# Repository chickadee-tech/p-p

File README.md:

# Chickadee Tech Pololu Power Polystack Board #
This power board provides power to the base control board. It can either be used by mounting a Pololu voltage regulator directly to the pins or by using wire to connect to an existing regulator.

## Documentation ##
See the [wiki](https://github.com/chickadee-tech/p-p/wiki) for documentation.

## Polystack ##
This **power** board is part of the Polystack platform for modular microcontrol systems. More information on the platform can be found at [polystack.org](http://polystack.org).

## Support ##
If you need support with a board you own or have development questions please email support@chickadee.tech or check [chickadee.tech/support](https://chickadee.tech/support) for other ways to get support.

## Contributing ##
Please note that this project is released with a [Contributor Code of Conduct](CODE_OF_CONDUCT.md). By participating in this project you agree to abide by its terms.

### Setup ###
Components and footprints for PCB parts are not included in this repository. Instead, checkout the [chickadee-tech/kicad-libs](https://github.com/chickadee-tech/kicad-libs) repository in the same directory that this repository is checked out in. All part definitions should be relative so that they will load correctly.

### Pull requests ###
For fixes please submit a pull request to the original repository. After the pull request is merged, check the [Chickadee Tech Active Contributor Discount (ACD)](https://chickadee.tech/active-contributor) to see if you are eligible for a discount code to use on your next purchase.

### Derivatives ###
If developing your own version of the Pololu Power board please remove all Chickadee Tech trademarks and follow the [CC-BY license](LICENSE). While not required, please consider open sourcing your modifications so others can learn from your improvements. If you do email support@chickadee.tech and we may choose to add your project to the ACD.

You may also license the Polystack logo for free by emailing support@chickadee.tech. We'll ask for your gerbers to ensure the design complies with specifications laid out [here](https://github.com/chickadee-tech/polystack/wiki) and provide written permission to use the trademark after compliance has been demonstrated.

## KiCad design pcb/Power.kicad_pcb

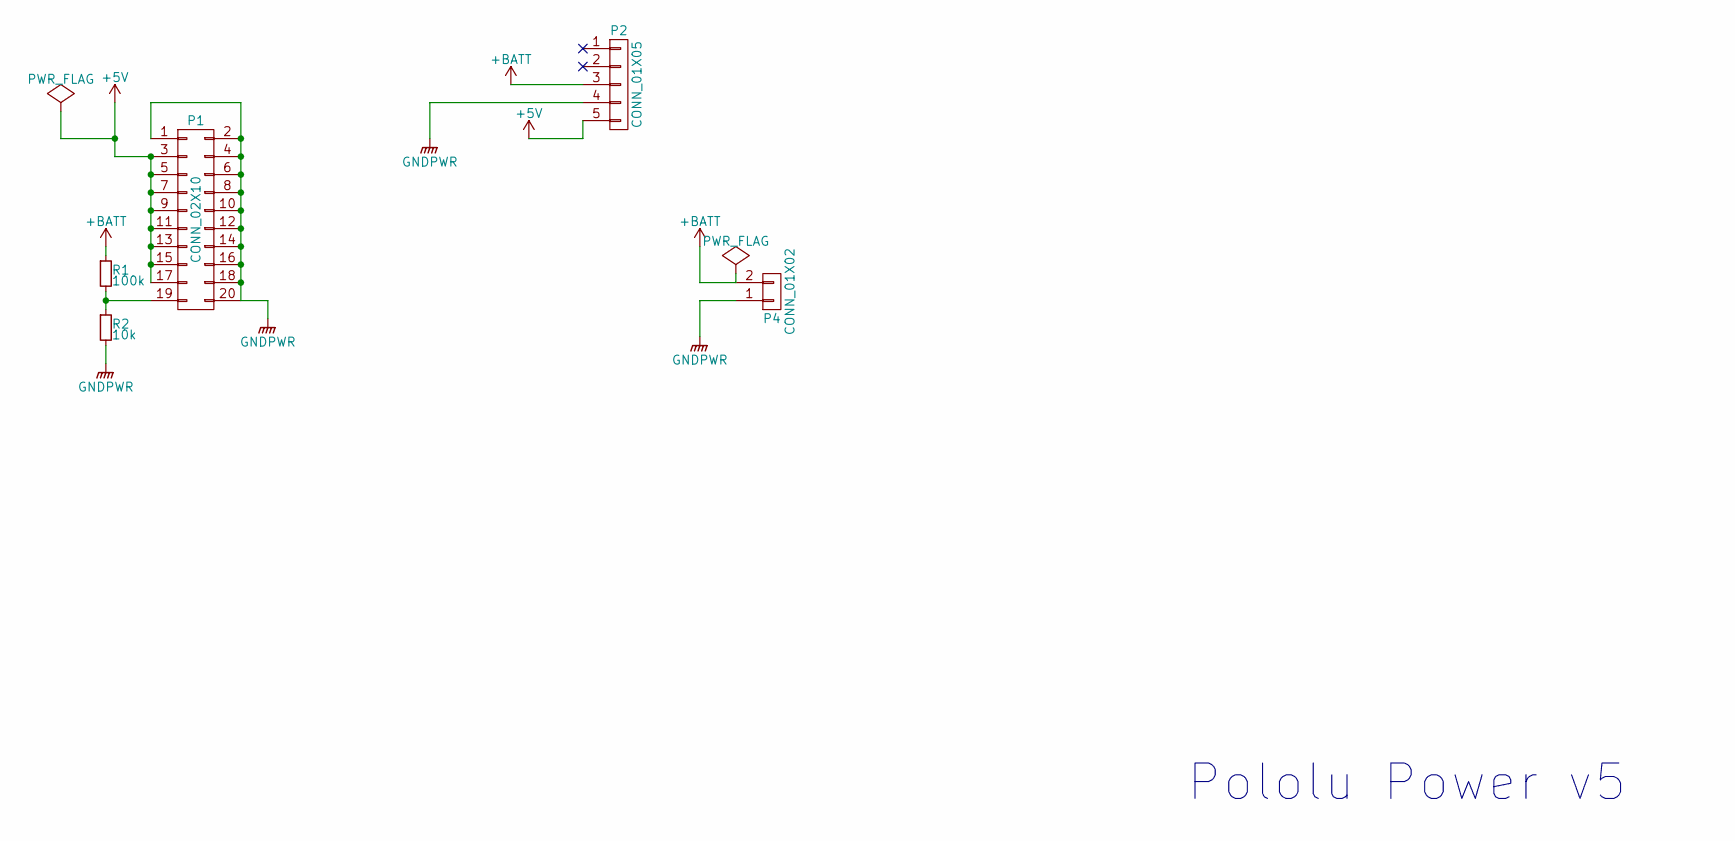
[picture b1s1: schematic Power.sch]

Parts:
P1: CONN_02X10; DF40-1.5mm-20pin-Receptacle
P2: CONN_01X05; Pin_Header_Straight_1x05
P4: CONN_01X02; 16awg_Pin_Header_Straight_1x02
R1: 100k; R_0603_HandSoldering
R2: 10k; R_0603_HandSoldering

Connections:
+5V: P1.3, P1.5, P1.7, P1.9, P1.11, P1.13, P1.15, P1.17, P2.5
+BATT: P2.3, P4.2, R1.1
GNDPWR: P1.1, P1.2, P1.4, P1.6, P1.8, P1.10, P1.12, P1.14, P1.16, P1.18, P1.20, P2.4, P4.1, R2.2
unnamed: P1.19, R1.2, R2.1

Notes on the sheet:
Pololu Power v5

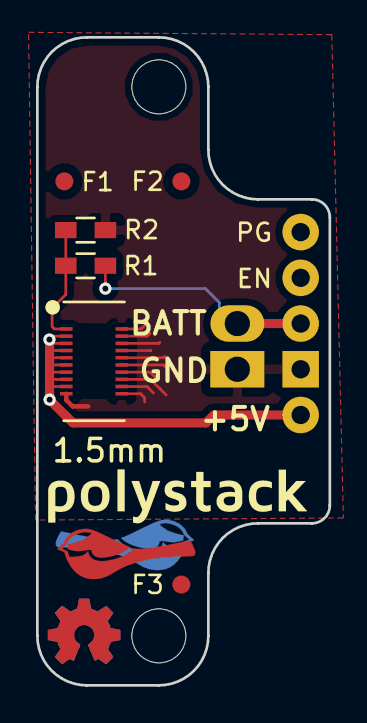
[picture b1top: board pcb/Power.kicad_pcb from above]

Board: 2 copper layers, 16.2 x 36.0 mm, 10 parts (1 on the bottom side), 4 nets.

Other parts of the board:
F1, F2, F3: 1mm; Fiducial
svg2mod, svg2mod#2: G***; polystack-bold-0.75

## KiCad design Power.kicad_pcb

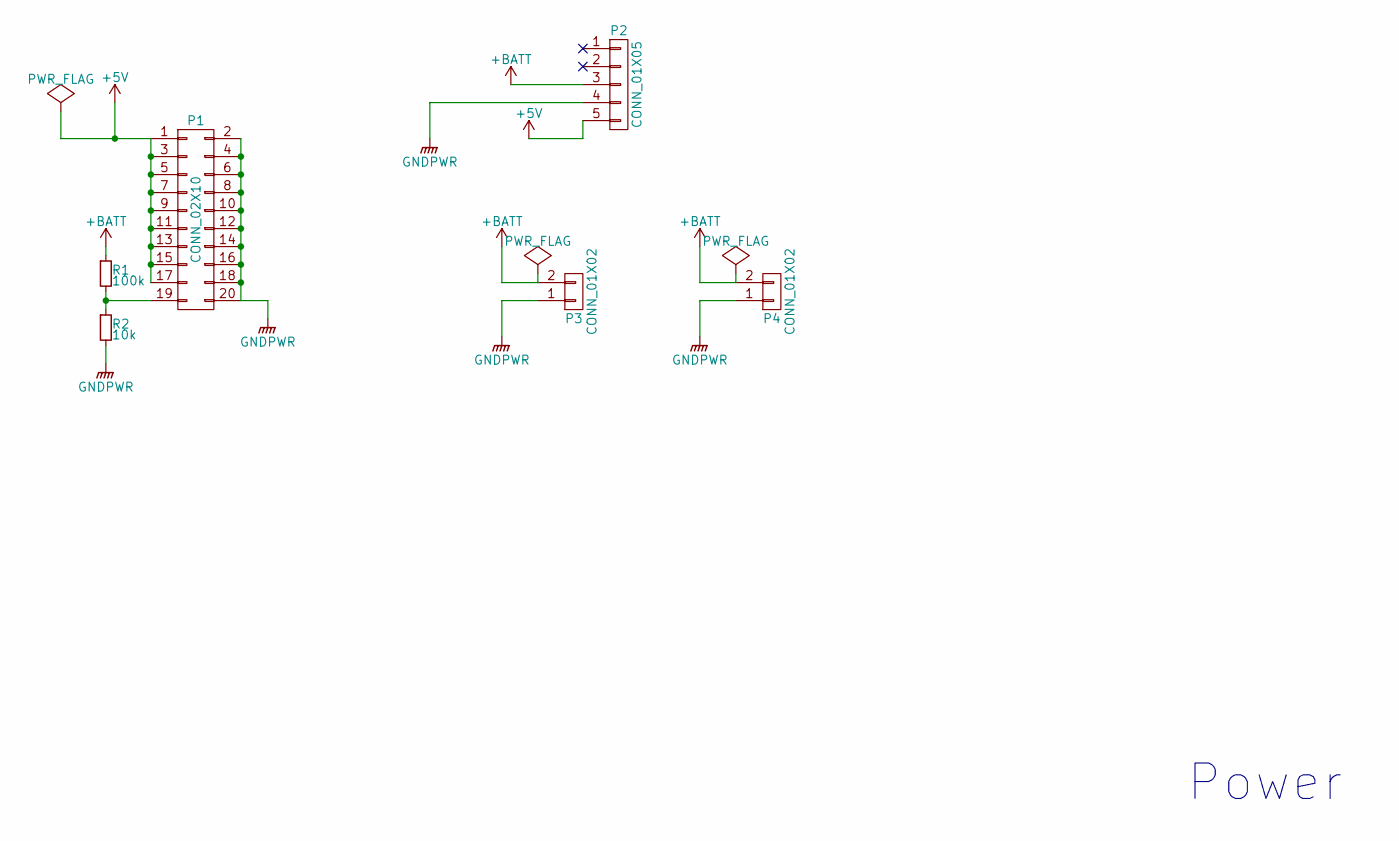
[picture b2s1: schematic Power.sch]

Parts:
P1: CONN_02X10; DF40-1.5mm-20pin-Receptacle
P2: CONN_01X05; Pin_Header_Straight_1x05
P3, P4: CONN_01X02; 16awg_Pin_Header_Straight_1x02
R1: 100k; R_0603_HandSoldering
R2: 10k; R_0603_HandSoldering

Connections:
+5V: P1.1, P1.3, P1.5, P1.7, P1.9, P1.11, P1.13, P1.15, P1.17, P2.5
+BATT: P2.3, P3.2, P4.2, R1.1
GNDPWR: P1.2, P1.4, P1.6, P1.8, P1.10, P1.12, P1.14, P1.16, P1.18, P1.20, P2.4, P3.1, P4.1, R2.2
unnamed: P1.19, R1.2, R2.1

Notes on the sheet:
Power

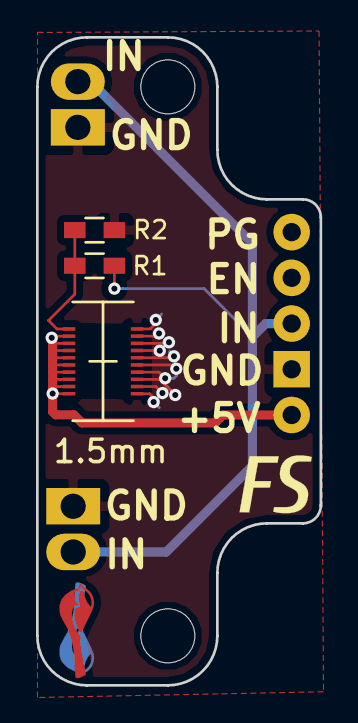
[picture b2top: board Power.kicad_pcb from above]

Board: 2 copper layers, 15.8 x 36.0 mm, 6 parts (0 on the bottom side), 4 nets.

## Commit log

2015-11-18 v1 of pololu power board
2016-01-11 Add voltage divider to pololu power
2016-01-26 Add a voltage divider for the battery to pololu power. Passing in full battery can leads to smoking regulators if it bridges to 5V.
2016-01-30 v3 of pololu power. Moved pololu headers to the board edge, centered it to fit narrow standoffs, switched 5v traces to outside to hopefully strengthen the solder joint, and make annular ring of power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
2016-03-05 Pololu Power v5 which moves the input holes back out from under the FC.
2016-04-07 Move everything over to pcb.
2016-04-13 Rebrand everything to Polystack and increment versions.
2016-04-16 Final gerbers for test manufacturing run.
2016-06-07 Update polystack logo to bold variant and bump version number.
2016-07-07 Add license information to many files. PCB design files are CC-BY and code is MIT license.
2016-07-07 Add back .gitignore after repo split.
2016-07-07 Convert to relative component and footprint paths.

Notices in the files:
pcb/Power.kicad_pcb:
Copyright 2016 Chickadee Tech LLC
This work is licensed under the Creative Commons Attribution 4.0 International License.
To view a copy of this license, visit http://creativecommons.org/licenses/by/4.0
or send a letter to Creative Commons, PO Box 1866, Mountain View, CA 94042, USA.
